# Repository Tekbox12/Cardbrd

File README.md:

# CardBrd

12 key macro pad built using ergogen v4

## Features

- QMK and VIA support
- 12 keys (4 rows 3 columns)
- rotary encoder with click
- reset button

## Materials
* 1x Pro micro
* 1x ec11 rotary encoder
* 1x reset switch (smd, 4 pin, flat)
* 12x 1N4148 Switches (smd or through hole)
* 12x any(i think) 5 pin mx switches
* 4x M2 x 3mm L x 3.2mm threaded brass inserts
* 4x M2 Laptop style flathead screw
## Firmware
[My QMK fork](https://github.com/Tekbox12/qmk_firmware/tree/dev_branch/keyboards/cardbrd)
OR Use the qmk files in the qmk folder

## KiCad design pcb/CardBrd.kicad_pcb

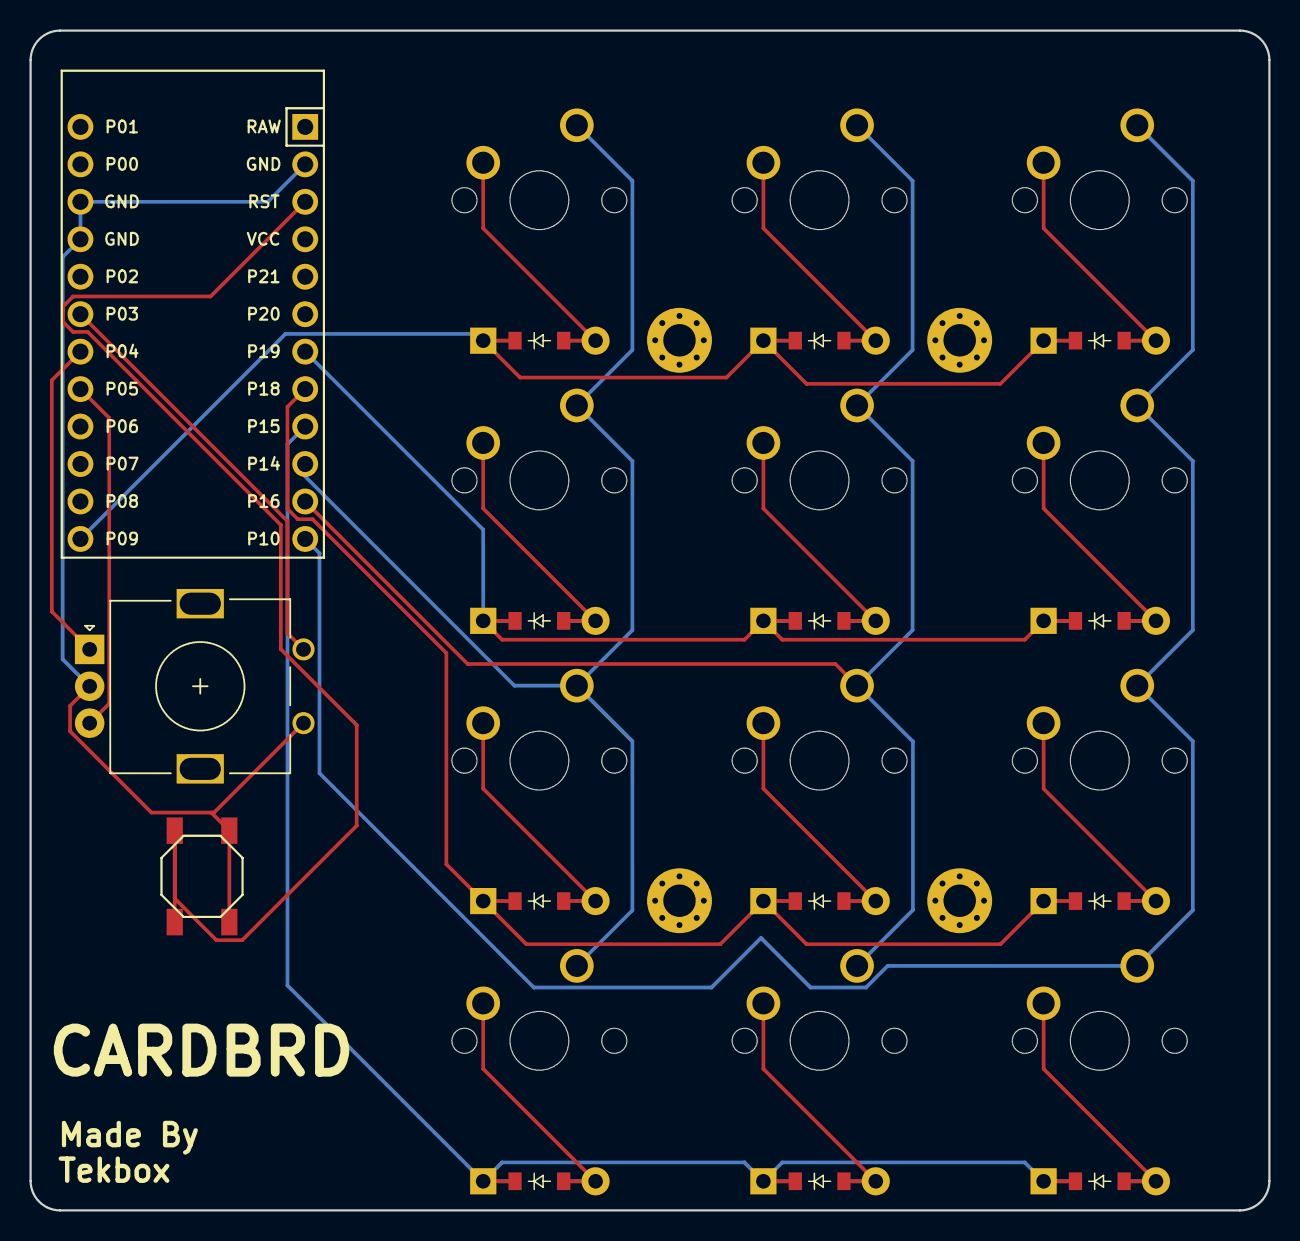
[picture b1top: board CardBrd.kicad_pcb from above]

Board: 2 copper layers, 84.0 x 80.0 mm, 31 parts (0 on the bottom side), 24 nets.

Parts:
B1: SW_TACT_ALPS_SKQGABE010
D1, D2, D3, D4, D5, D6, D7, D8, D9, D10, D11, D12: ComboDiode
MCU1: ProMicro
ROT1: rotary_encoder
S1, S2, S3, S4, S5, S6, S7, S8, S9, S10, S11, S12: MX
_1, _2, _3, _4: MountingHole_2.2mm_M2_Pad_Via

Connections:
GND: B1.1, MCU1.2, MCU1.15, MCU1.16, ROT1.2, ROT1.C
P3: MCU1.18, ROT1.1
P4: MCU1.19, ROT1.A
P5: MCU1.20, ROT1.B
P9: D4.1, D8.1, D12.1, MCU1.24
P10: MCU1.12, S9.1, S10.1, S11.1, S12.1
P14: MCU1.10, S1.1, S2.1, S3.1, S4.1
P15: D1.1, D5.1, D9.1, MCU1.9
P16: MCU1.11, S5.1, S6.1, S7.1, S8.1
P18: D2.1, D6.1, D10.1, MCU1.8
P19: D3.1, D7.1, D11.1, MCU1.7
RST: B1.2, MCU1.3
left_four: D12.2, S12.2
left_one: D9.2, S9.2
left_three: D11.2, S11.2
left_two: D10.2, S10.2
middle_four: D8.2, S8.2
middle_one: D5.2, S5.2
middle_three: D7.2, S7.2
middle_two: D6.2, S6.2
right_four: D4.2, S4.2
right_one: D1.2, S1.2
right_three: D3.2, S3.2
right_two: D2.2, S2.2
